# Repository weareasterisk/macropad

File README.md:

# How to Make a Macropad
Ever wanted to build your own macro pad? Well, we did and it's really cool! This repo contains the files we used to build it. Check out how we got started in our youtube series!

[How to Make a Macro Pad](https://www.youtube.com/watch?v=piywYCbLJUU)

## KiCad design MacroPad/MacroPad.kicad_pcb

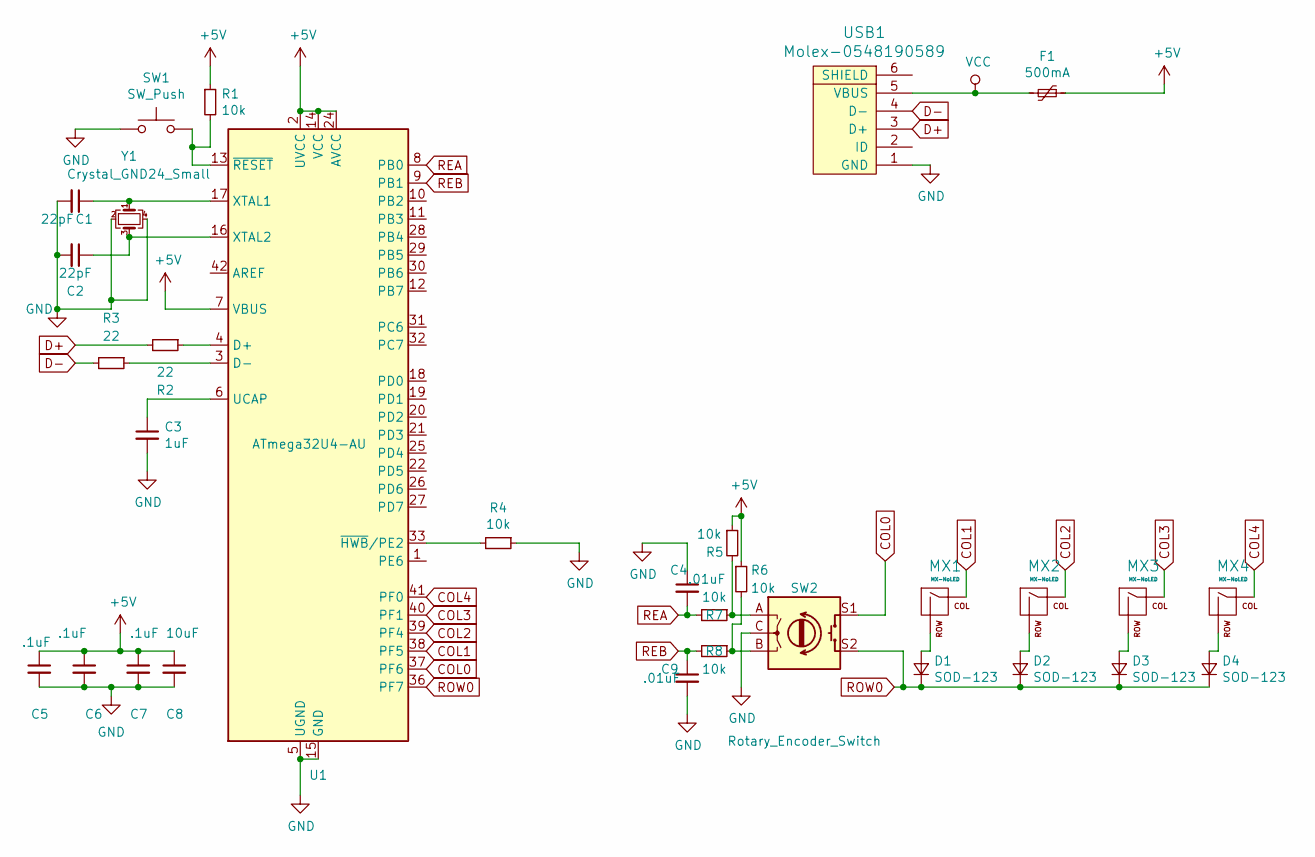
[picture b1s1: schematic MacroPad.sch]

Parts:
C1, C2: 22pF; C_0805_2012Metric_Pad1.15x1.40mm_HandSolder
C3: 1uF; C_0805_2012Metric_Pad1.15x1.40mm_HandSolder
C4, C9: .01uF; C_0805_2012Metric_Pad1.15x1.40mm_HandSolder
C5, C6, C7: .1uF; C_0805_2012Metric_Pad1.15x1.40mm_HandSolder
C8: 10uF; C_0805_2012Metric_Pad1.15x1.40mm_HandSolder
D1, D2, D3, D4: SOD-123; D_SOD-123
F1: 500mA; Fuse_1206_3216Metric_Pad1.42x1.75mm_HandSolder
MX1, MX2, MX3, MX4: MX-NoLED; MX-1U-NoLED
R1, R4, R5, R6, R7, R8: 10k; R_0805_2012Metric_Pad1.15x1.40mm_HandSolder
R2, R3: 22; R_0805_2012Metric_Pad1.15x1.40mm_HandSolder
SW1: SW_Push; SKQG-1155865
SW2: Rotary_Encoder_Switch; RotaryEncoder_Alps_EC11E-Switch_Vertical_H20mm
U1: ATmega32U4-AU; TQFP-44_10x10mm_P0.8mm
USB1: Molex-0548190589
Y1: Crystal_GND24_Small; Crystal_SMD_3225-4Pin_3.2x2.5mm_HandSoldering

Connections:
+5V: C5.1, C6.1, C7.1, C8.1, F1.1, R1.1, R5.1, R6.1, U1.2 (UVCC), U1.7 (VBUS), U1.14 (VCC), U1.24 (AVCC), U1.34 (VCC), U1.44 (AVCC)
COL0: SW2.S1, U1.37 (PF6)
COL1: MX1.1 (COL), U1.38 (PF5)
COL2: MX2.1 (COL), U1.39 (PF4)
COL3: MX3.1 (COL), U1.40 (PF1)
COL4: MX4.1 (COL), U1.41 (PF0)
D+: R2.2, USB1.3 (D+)
D-: R3.2, USB1.4 (D-)
GND: C1.2, C2.2, C3.2, C4.1, C5.2, C6.2, C7.2, C8.2, C9.2, R4.1, SW1.1, SW2.C, U1.5 (UGND), U1.15 (GND), U1.23 (GND), U1.35 (GND), U1.43 (GND), USB1.1 (GND), Y1.2, Y1.4
unnamed: C1.1, U1.17 (XTAL1), Y1.1
unnamed: C2.1, U1.16 (XTAL2), Y1.3
unnamed: C3.1, U1.6 (UCAP)
unnamed: D1.2 (A), MX1.2 (ROW)
unnamed: D2.2 (A), MX2.2 (ROW)
unnamed: D3.2 (A), MX3.2 (ROW)
unnamed: D4.2 (A), MX4.2 (ROW)
unnamed: R1.2, SW1.2, U1.13 (~RESET)
unnamed: R2.1, U1.4 (D+)
unnamed: R3.1, U1.3 (D-)
unnamed: R4.2, U1.33 (~HWB~/PE2)
unnamed: R5.2, R7.1, SW2.A
unnamed: R6.2, R8.1, SW2.B
REA: C4.2, R7.2, U1.8 (PB0)
REB: C9.1, R8.2, U1.9 (PB1)
ROW0: D1.1 (K), D2.1 (K), D3.1 (K), D4.1 (K), SW2.S2, U1.36 (PF7)
VCC: F1.2, USB1.5 (VBUS)

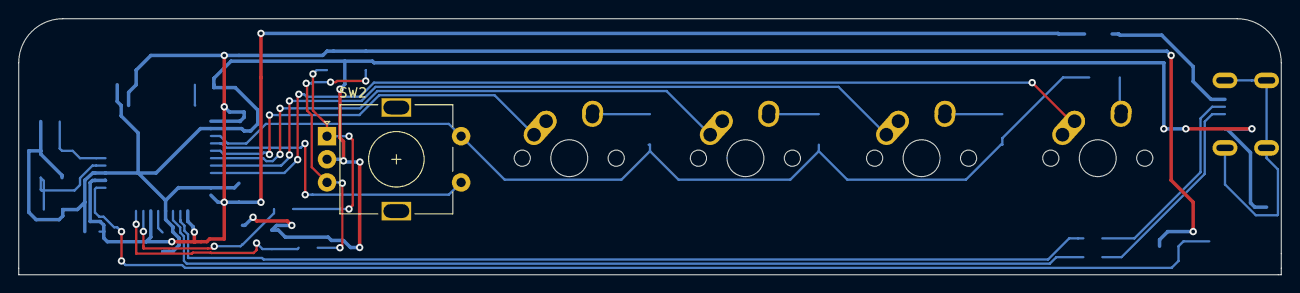
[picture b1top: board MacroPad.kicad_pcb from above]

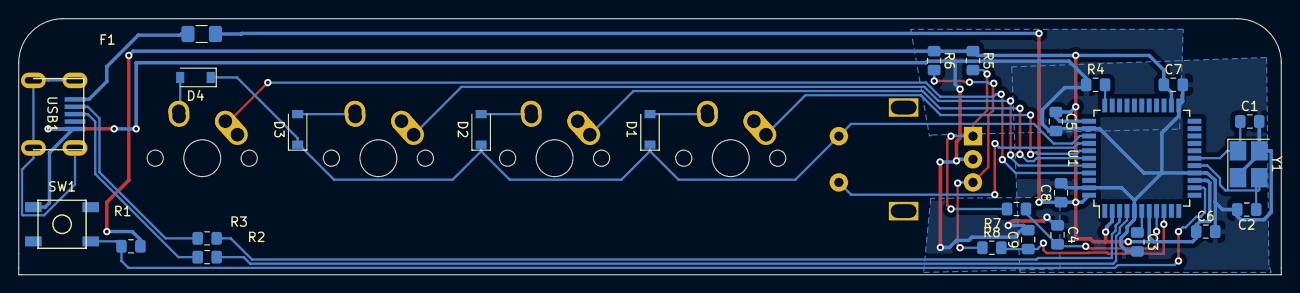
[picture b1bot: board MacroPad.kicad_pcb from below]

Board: 2 copper layers, 136.5 x 27.7 mm, 31 parts (26 on the bottom side), 26 nets.

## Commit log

2020-04-12 Intialize repo
2020-04-12 Add submodules
2020-04-12 Add Libraries
2020-05-29 Add digikey lib submodule
2020-06-04 Add files\nGet component links mostly finished
2020-06-05 Route all traces
2020-06-05 Design check
2020-06-07 Add Gerbers
